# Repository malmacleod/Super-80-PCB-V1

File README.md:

# Super-80 PCB (V1)

This repository stores the KiCad files (schematic and PCB) for the work-in-progress task of creating a reproduction of the Super 80 Computer.

The schematic is fully drawn.

As at 11-OCT-2016, the PCB is about 50% completed.

This will be as close a copy as possible to the original design.  Once this board has been completed, a slightly modified version will then be created, to overcome problems associated with components that are no longer available (such as the keyswitches).

STATUS:

11-OCT-2016: Added bottom layer traces in the vicinity of the 3 24-pin ICs U26, U33 and U42.

10-OCT-2016: Initial upload of KiCad files to Github.

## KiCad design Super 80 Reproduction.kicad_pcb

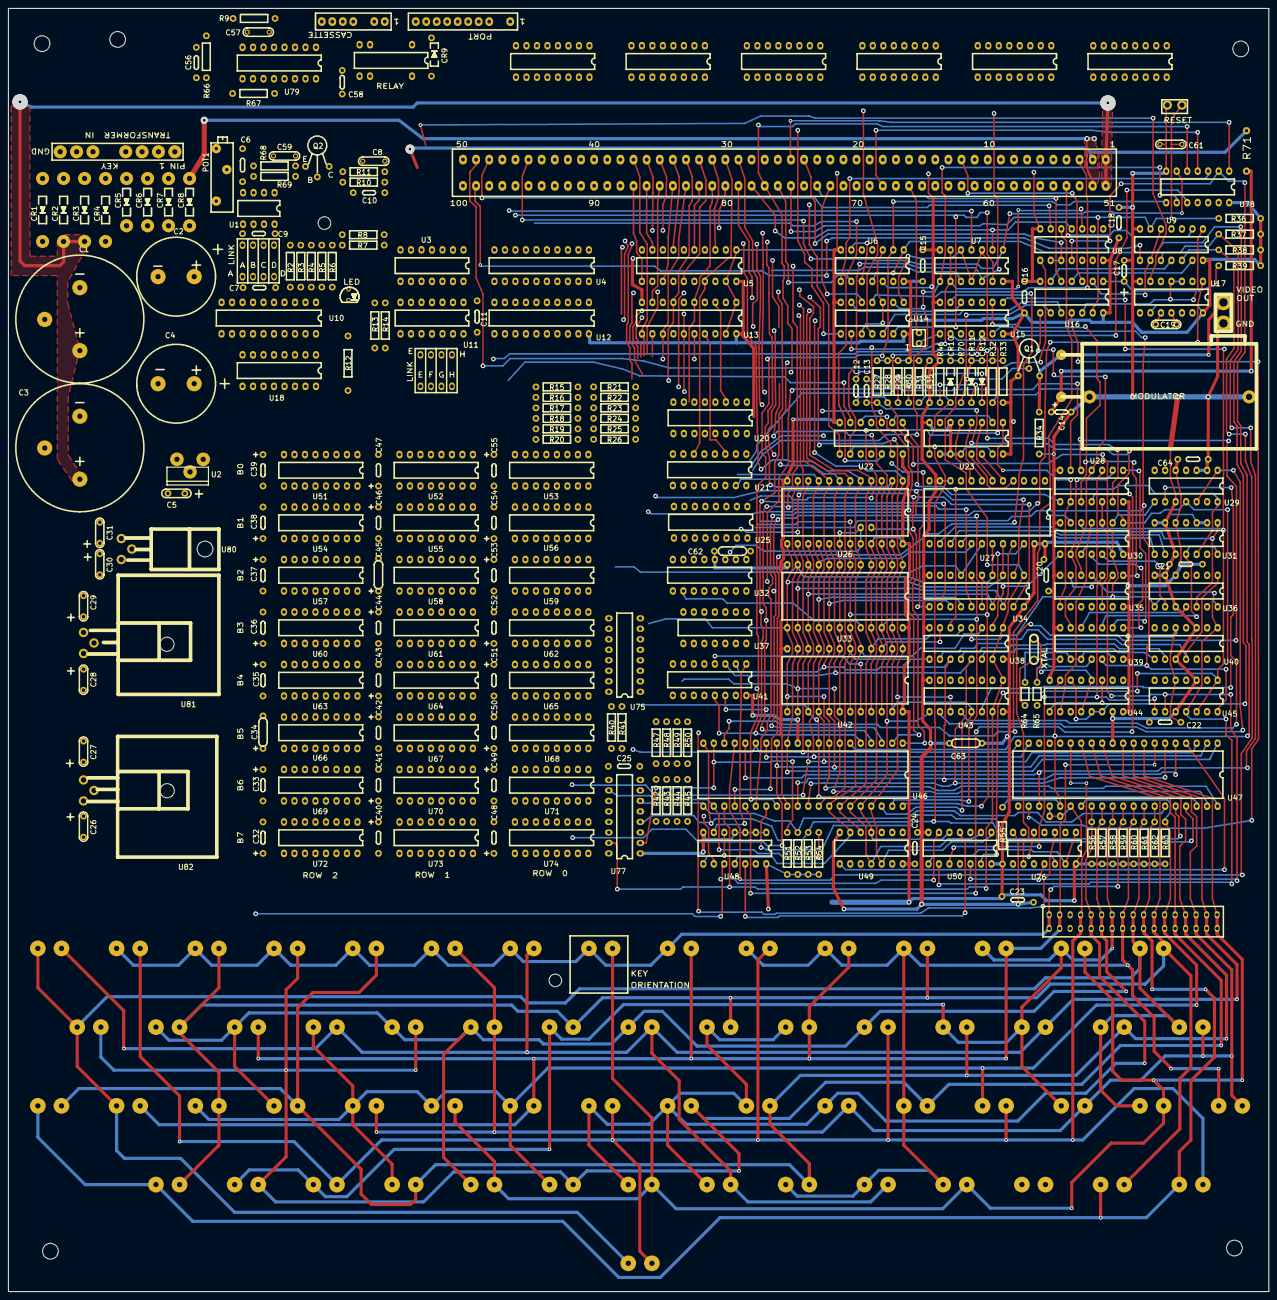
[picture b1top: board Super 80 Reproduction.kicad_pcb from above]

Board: 2 copper layers, 305.0 x 310.5 mm, 312 parts (0 on the bottom side), 281 nets.

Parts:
C1, C3: 5600uF; S80-C1220-POL-600
C2: 1000uF; S80-C2-750-345
C4: 1000uF; S80-C4-750-345
C5: 10uF; S80-C160-POL-32
C6, C21: 0.1uF; S80-C315-32
C7, C9, C63: 0.1uF; S80-C310-32
C8, C57, C59: 0.01uF; S80-C210-32
C10, C11, C15, C16, C22, C25: 0.1uF; S80-C300-32
C12: 68pF; S80-C225-32
C13: 0.01uF; S80-C225-32
C14: 25uF 25V; S80-C190-POL-32
C17: 33uF TANT; S80-C17-200-32
C18, C56, C64: 0.1uF; S80-C290-32
C19: 0.1uF; S80-C200-32-2
C20: 0.1uF; S80-C20-300-32
C23: 0.1uF; S80-C23-300-32
C24: 0.1uF; S80-C24-300-32
C26, C27, C28, C29, C30, C31: 10uF; S80-C200-32-2
C32, C36, C43, C47, C48, C52: 0.1uF; S80-C300-POL-32-A1
C33, C37, C42, C46, C49, C53: 1.5uF TANT; S80-C300-POL-32-B1
C34, C45: 15uF TANT; S80-C310-POL-32-A1
C35, C39, C40, C44, C51, C55: 0.1uF; S80-C300-POL-32-B1
C38, C41, C50, C54: 15uF TANT; S80-C300-POL-32-A1
C58: 0.1uF; S80-C255-32
C61: 0.1uF; S80-C210-32
C62: 0.1uF; S80-C345-32
CR1, CR2, CR3, CR4: MUR420G; S80-D600-50
CR5, CR6, CR7, CR8: 1N4001; S80-D450-50
CR9: 1N914; S80-D365-32
CR10, CR11, CR12: 1N914; S80-D400-32
J1: 8 PIN HEADER; S80-J1-TRANSFORMER
J2: 7 PIN HEADER; S80-J2-CASSETTE
J3: 10 PIN HEADER; S80-J3-PORT
J4: 2 PIN HEADER; S80-J4-VIDEO
J5: S-100 CONNECTOR; S80-S100-CONNECTOR
J6: KEYBOARD CONNECTOR; S80-J6-KEYBRD
JP1: S80-LINK
JP2: JUMPER; S80-JP2
JP3: PRE-LINK; S80-LINK
KEY1, KEY2, KEY3, KEY4, KEY5, KEY6, KEY7, KEY9, KEY10, KEY11, KEY12, KEY13, KEY14, KEY15, KEY16, KEY17, KEY18, KEY19, KEY20, KEY21, KEY22, KEY23, KEY24, KEY25, KEY26, KEY27, KEY28, KEY29, KEY30, KEY32, KEY33, KEY34, KEY35, KEY36, KEY37, KEY38, KEY39, KEY40, KEY41, KEY42, KEY43, KEY44, KEY45, KEY46, KEY48, KEY49, KEY50, KEY51, KEY52, KEY53, KEY54, KEY55, KEY56, KEY57, KEY60, KEY100: S80-KEYSW-A; S80-KEYSW
KEY8: S80-KEYSW-A; S80-KEYSW-OUTLINE
KEY31, KEY47, KEY58, KEY59: S80-KEYSW-B; S80-KEYSW
LED1: 5MM RED LED; S80-LED1
MOD1: UM1082AUS; S80-RF-MOD-ORIG
POT1: 20K; S80-POT1
Q1: BC548; S80-Q1
Q2: BC327; S80-Q2
R2, R3, R4, R5, R6, R36, R39, R56, R57, R58, R59, R60, R61, R62, R63: 4.7K; S80-R400-32
R7: 100K; S80-R400-32
R8: 150R; S80-R400-32
R9: 270K; S80-R400-32
R10, R33, R51, R52, R53, R54: 10K; S80-R400-32
R11: 100R; S80-R400-32
R12: 180R; S80-R520-32
R13: 330; S80-R430-32
R14: 33; S80-R430-32
R15, R16, R17, R18, R19, R20, R41, R42, R43, R44, R45: 33R; S80-R400-32
R21, R22, R23, R24, R25, R26, R31, R40, R47, R48, R49, R50: 330R; S80-R400-32
R27, R28: 2.2K; S80-R400-32
R29, R30: 33K; S80-R400-32
R32, R70: 3.3K; S80-R400-32
R34: 56R; S80-R400-32
R35, R46: 15K; S80-R400-32
R37, R38: 1K; S80-R400-32
R55: 330R; S80-R540-32
R64, R65: 1K; S80-R220-32
R66: 22K; S80-R400-32
R67: 27K; S80-R400-32
R68: 47K; S80-R400-32
R69: 68K; S80-R400-32
R71: 270R 1W ??; S80-R71-385-32
RELAY1: 14-PIN DIL 5V SPDT RELAY; S80-RELAY-DIP-14
Ref**: H*; S80-HOLE-150
Ref**#2, Ref**#3: H*; S80-HOLE-120
Ref**#4, Ref**#5, Ref**#6, Ref**#7: H*; S80-HOLE-150
SW1: 4-WAY DIP SWITCH; S80-SW1-ABCD
SW2: 4-WAY DIP SWITCH; S80-SW2-EFGH
SW3: PCB MOM SW 2-PIN; S80-SW-RESET
U1: LM311; S80-DIP-8-300
U2: 7905T; S80-U2-7905
U3, U7, U78: 74LS02; S80-DIP-14-300
U4, U5, U10, U12, U13: 81LS95; S80-DIP-20-300
U6, U76: 74LS74; S80-DIP-14-300
U8, U15, U22, U39: 74LS04; S80-DIP-14-300
U9: 74LS05; S80-DIP-14-300
U11, U35, U49: 74LS30; S80-DIP-14-300
U14, U28, U37: 74LS00; S80-DIP-14-300
U16: 74LS14; S80-DIP-14-300
U17: 74121; S80-DIP-14-300
U18: 74LS174; S80-DIP-16-300
U20, U21: 74157; S80-DIP-16-300
U23: 74LS165; S80-DIP-16-300
U25, U44, U75: 74109; S80-DIP-16-300
U26: 2516 or 2532; S80-DIP-24-600
U27: 2513; S80-DIP-24-600
U29, U40, U45: 74LS93; S80-DIP-14-300
U30: 74LS86; S80-DIP-14-300
U31: 74LS90; S80-DIP-14-300
U32: 74LS138; S80-DIP-16-300
U33, U42: 2532; S80-DIP-24-600
U34: 74LS374; S80-DIP-20-300
U36: 74LS92; S80-DIP-14-300
U38, U43, U77: 74LS367; S80-DIP-16-300
U41: 74LS139; S80-DIP-16-300
U46: Z80 CPU; S80-DIP-40-600
U47: Z80 PIO; S80-DIP-40-600
U48: 74LS27; S80-DIP-14-300
U50: 74LS20; S80-DIP-14-300
U51, U52, U53, U54, U55, U56, U57, U58, U59, U60, U61, U62, U63, U64, U65, U66, U67, U68, U69, U70, U71, U72, U73, U74: 4116; S80-DIP-16-300
U79: 4046; S80-DIP-16-300
U80: 7812T; S80-U80-7812
U81: 7805T; S80-U81-7805
U82: 7805T; S80-U82-7805
XTAL1: 12MHz; S80-XTAL

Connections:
6LATCH*: U22.5, U41.4
12MHz: U15.13, U25.12, U39.12, U45.14
12MHz*: U15.12, U25.4, U75.4, U75.12, U76.3
+8V: C1.1, C3.1, C27.1, C29.1, CR2.2, CR3.2, J5.1, J5.51, U81.VI, U82.VI
+16V: C2.1, C31.1, CR6.2, CR7.2, J3.3, J5.2, R71.1, U80.VI
-16V: C4.2, CR5.1, CR8.1, J3.1, J5.52, U2.VI
/CPU & ROM/A0: U13.2, U26.8, U33.8, U38.11, U41.2, U42.8, U46.30, U47.5
/CPU & ROM/A1: U13.16, U26.7, U33.7, U38.13, U41.3, U42.7, U46.31, U47.6
/CPU & ROM/A2: U13.4, U26.6, U33.6, U38.9, U42.6, U46.32
/CPU & ROM/A3: U5.2, U26.5, U33.5, U38.3, U42.5, U46.33, U48.11, U49.6
/CPU & ROM/A4: U5.18, U26.4, U33.4, U38.5, U42.4, U46.34, U49.5
/CPU & ROM/A5: U13.18, U26.3, U33.3, U38.7, U42.3, U46.35, U49.11, U50.2
/CPU & ROM/A6: U5.4, U26.2, U33.2, U42.2, U43.9, U46.36, U49.4, U50.5
/CPU & ROM/A7: U13.14, U26.1, U33.1, U42.1, U43.11, U46.37, U49.12, U50.1
/CPU & ROM/A8: U5.14, U26.23, U33.23, U42.23, U43.13, U46.38
/CPU & ROM/A9: U5.6, U26.22, U33.22, U34.6, U42.22, U46.39
/CPU & ROM/A10: U13.12, U26.19, U33.19, U34.5, U42.19, U46.40
/CPU & ROM/A11: JP1.2, U5.12, U34.2, U46.1
/CPU & ROM/A12: U13.6, U32.1, U34.19, U46.2
/CPU & ROM/A13: U13.8, U32.2, U34.16, U46.3
/CPU & ROM/A14: U5.8, U34.15, U37.2, U41.14, U46.4
/CPU & ROM/A15: U5.16, U34.12, U37.1, U41.13, U46.5
/CPU & ROM/D0: U4.11, U10.3, U12.12, U18.3, U26.9, U27.17, U33.9, U42.9, U46.14, U47.19, U51.2, U51.14, U52.2, U52.14, U53.2, U53.14
/CPU & ROM/D1: U4.9, U10.9, U12.8, U18.4, U26.10, U27.18, U33.10, U34.7, U42.10, U46.15, U47.20, U54.2, U54.14, U55.2, U55.14, U56.2, U56.14
/CPU & ROM/D2: U4.17, U10.13, U12.18, U18.6, U26.11, U27.19, U33.11, U34.4, U42.11, U46.12, U47.1, U57.2, U57.14, U58.2, U58.14, U59.2, U59.14
/CPU & ROM/D3: U4.15, U12.16, U18.11, U26.13, U27.20, U33.13, U34.3, U42.13, U46.8, U47.40, U60.2, U60.14, U61.2, U61.14, U62.2, U62.14
/CPU & ROM/D4: U4.3, U10.17, U12.2, U18.13, U26.14, U27.21, U33.14, U34.18, U42.14, U46.7, U47.39, U63.2, U63.14, U64.2, U64.14, U65.2, U65.14
/CPU & ROM/D5: U4.5, U10.5, U12.4, U18.14, U26.15, U27.22, U33.15, U34.17, U42.15, U46.9, U47.38, U66.2, U66.14, U67.2, U67.14, U68.2, U68.14
/CPU & ROM/D6: U4.7, U10.15, U12.6, U26.16, U33.16, U34.14, U42.16, U46.10, U47.3, U69.2, U69.14, U70.2, U70.14, U71.2, U71.14
/CPU & ROM/D7: U4.13, U10.7, U12.14, U26.17, U33.17, U34.13, U42.17, U46.13, U47.2, U72.2, U72.14, U73.2, U73.14, U74.2, U74.14
/CPU & ROM/IOREQ*: R53.1, U46.20, U47.36, U77.4
/CPU & ROM/MEMREQ*: R51.1, U46.19, U77.2
/CPU & ROM/PA0: J6.7, J6.8, KEY2.2, KEY10.2, KEY26.2, KEY38.2, KEY43.2, KEY49.2, KEY59.2, KEY60.2, U47.15
/CPU & ROM/PA1: J6.21, J6.22, KEY3.2, KEY12.2, KEY15.2, KEY17.2, KEY22.2, KEY24.2, KEY33.2, KEY47.2, KEY58.2, U47.14
/CPU & ROM/PA2: J6.25, J6.26, KEY4.2, KEY16.2, KEY20.2, KEY39.2, KEY42.2, KEY48.2, KEY52.2, U47.13
/CPU & ROM/PA3: J6.27, J6.28, KEY5.2, KEY27.2, KEY29.2, KEY31.2, KEY34.2, KEY40.2, KEY50.2, KEY55.2, U47.12
/CPU & ROM/PA4: J6.29, J6.30, KEY6.2, KEY21.2, KEY30.2, KEY35.2, KEY41.2, KEY44.2, KEY46.2, U47.10
/CPU & ROM/PA5: J6.31, J6.32, KEY1.2, KEY7.2, KEY19.2, KEY23.2, KEY28.2, KEY54.2, KEY56.2, U47.9
/CPU & ROM/PA6: J6.33, J6.34, KEY8.2, KEY14.2, KEY36.2, KEY45.2, KEY51.2, KEY53.2, KEY57.2, U47.8
/CPU & ROM/PA7: J6.3, J6.4, KEY9.2, KEY11.2, KEY13.2, KEY18.2, KEY25.2, KEY32.2, KEY37.2, U47.7
/CPU & ROM/PB0: J6.23, J6.24, KEY19.1, KEY33.1, KEY35.1, KEY36.1, KEY37.1, KEY43.1, KEY50.1, KEY52.1, R63.1, U47.27
/CPU & ROM/PB1: J6.9, J6.10, KEY24.1, KEY25.1, KEY38.1, KEY39.1, KEY40.1, KEY41.1, KEY53.1, KEY54.1, R56.1, U47.28
/CPU & ROM/PB2: J6.11, J6.12, KEY17.1, KEY18.1, KEY20.1, KEY21.1, KEY23.1, KEY26.1, KEY34.1, KEY51.1, R57.1, U47.29
/CPU & ROM/PB3: J6.13, J6.14, KEY13.1, KEY14.1, KEY22.1, KEY27.1, KEY28.1, KEY44.1, KEY48.1, KEY49.1, R58.1, U47.30
/CPU & ROM/PB4: J6.1, J6.2, KEY2.1, KEY3.1, KEY4.1, KEY5.1, KEY6.1, KEY7.1, KEY8.1, KEY9.1, R59.1, U47.31
/CPU & ROM/PB5: J6.15, J6.16, KEY10.1, KEY11.1, KEY12.1, KEY42.1, KEY46.1, KEY55.1, KEY56.1, KEY57.1, R60.1, U47.32
/CPU & ROM/PB6: J6.17, J6.18, KEY1.1, KEY15.1, KEY16.1, KEY29.1, KEY30.1, KEY32.1, KEY45.1, KEY60.1, R61.1, U47.33
/CPU & ROM/PB7: J6.19, J6.20, KEY31.1, KEY47.1, KEY58.1, KEY59.1, R62.1, U47.34
/CPU & ROM/RD*: R52.1, U46.21, U47.35, U77.6, U77.11
/CPU & ROM/WR*: R54.1, U46.22, U77.10
/I/O/32K*: R3.1, SW1.6, U10.16
/I/O/48K*: R2.1, SW1.5, U10.6
/I/O/JP BASIC*: R4.1, SW1.7, U10.4
/I/O/PORT-5: J3.5, U18.12
/I/O/PORT-6: J3.6, U18.10
/I/O/PORT-7: J3.7, U10.8
/I/O/PORT-8: J3.8, U10.14
/I/O/TEST*: R5.1, SW1.8, U10.18
/RAM/AA0: R16.2, R22.1, U20.4
/RAM/AA1: R15.2, R21.1, U20.7
/RAM/AA2: R18.2, R24.1, U20.9
/RAM/AA3: R17.2, R23.1, U20.12
/RAM/AA4: R20.2, R26.1, U21.7
/RAM/AA5: R19.2, R25.1, U21.4
/RAM/AA6: R40.1, R41.1, U21.9
/RAM/BAA0: R16.1, U51.5, U52.5, U53.5, U54.5, U55.5, U56.5, U57.5, U58.5, U59.5, U60.5, U61.5, U62.5, U63.5, U64.5, U65.5, U66.5, U67.5, U68.5, U69.5, U70.5, U71.5, U72.5, U73.5, U74.5
/RAM/BAA1: R15.1, U51.12, U52.12, U53.12, U54.12, U55.12, U56.12, U57.12, U58.12, U59.12, U60.12, U61.12, U62.12, U63.12, U64.12, U65.12, U66.12, U67.12, U68.12, U69.12, U70.12, U71.12, U72.12, U73.12, U74.12
/RAM/BAA2: R18.1, U51.6, U52.6, U53.6, U54.6, U55.6, U56.6, U57.6, U58.6, U59.6, U60.6, U61.6, U62.6, U63.6, U64.6, U65.6, U66.6, U67.6, U68.6, U69.6, U70.6, U71.6, U72.6, U73.6, U74.6
/RAM/BAA3: R17.1, U51.11, U52.11, U53.11, U54.11, U55.11, U56.11, U57.11, U58.11, U59.11, U60.11, U61.11, U62.11, U63.11, U64.11, U65.11, U66.11, U67.11, U68.11, U69.11, U70.11, U71.11, U72.11, U73.11, U74.11
/RAM/BAA4: R20.1, U51.7, U52.7, U53.7, U54.7, U55.7, U56.7, U57.7, U58.7, U59.7, U60.7, U61.7, U62.7, U63.7, U64.7, U65.7, U66.7, U67.7, U68.7, U69.7, U70.7, U71.7, U72.7, U73.7, U74.7
/RAM/BAA5: R19.1, U51.10, U52.10, U53.10, U54.10, U55.10, U56.10, U57.10, U58.10, U59.10, U60.10, U61.10, U62.10, U63.10, U64.10, U65.10, U66.10, U67.10, U68.10, U69.10, U70.10, U71.10, U72.10, U73.10, U74.10
/RAM/BAA6: R41.2, U51.13, U52.13, U53.13, U54.13, U55.13, U56.13, U57.13, U58.13, U59.13, U60.13, U61.13, U62.13, U63.13, U64.13, U65.13, U66.13, U67.13, U68.13, U69.13, U70.13, U71.13, U72.13, U73.13, U74.13
/RAM/CAS0*: R45.2, U53.15, U56.15, U59.15, U62.15, U65.15, U68.15, U71.15, U74.15
/RAM/CAS1*: R44.2, U52.15, U55.15, U58.15, U61.15, U64.15, U67.15, U70.15, U73.15
/RAM/CAS2*: R43.2, U51.15, U54.15, U57.15, U60.15, U63.15, U66.15, U69.15, U72.15
/RAM/RAS*: R42.2, U51.4, U52.4, U53.4, U54.4, U55.4, U56.4, U57.4, U58.4, U59.4, U60.4, U61.4, U62.4, U63.4, U64.4, U65.4, U66.4, U67.4, U68.4, U69.4, U70.4, U71.4, U72.4, U73.4, U74.4
/RAM/S100-A0: J5.79, U13.3, U20.3
/RAM/S100-A1: J5.80, U13.15, U20.6
/RAM/S100-A2: J5.81, U13.5, U20.10
/RAM/S100-A3: J5.31, U5.3, U20.13
/RAM/S100-A4: J5.30, U5.17, U21.6
/RAM/S100-A5: J5.29, U13.17, U21.3
/RAM/S100-A6: J5.82, U5.5, U21.10
/RAM/S100-A7: J5.83, U13.13, U20.2
/RAM/S100-A8: J5.84, U5.13, U20.5
/RAM/S100-A9: J5.34, U5.7, U20.11
/RAM/S100-A10: J5.37, U13.11, U20.14
/RAM/S100-A11: J5.87, U5.11, U21.5
/RAM/S100-A12: J5.33, U13.7, U21.2
/RAM/S100-A13: J5.85, U13.9, U21.11
/S-100 Interface/S100-A14: J5.86, U5.9
/S-100 Interface/S100-A15: J5.32, U5.15
/S-100 Interface/S100-CLK-B*: J5.24, U8.9, U8.10
/S-100 Interface/S100-CLOCK-B*: J5.49, U8.8
/S-100 Interface/S100-DI0: J5.95, U4.12
/S-100 Interface/S100-DI1: J5.94, U4.8
/S-100 Interface/S100-DI2: J5.41, U4.18
/S-100 Interface/S100-DI3: J5.42, U4.16
/S-100 Interface/S100-DI4: J5.91, U4.2
/S-100 Interface/S100-DI5: J5.92, U4.4
/S-100 Interface/S100-DI6: J5.93, U4.6
/S-100 Interface/S100-DI7: J5.43, U4.14
/S-100 Interface/S100-DIN*: U4.19, U11.8
/S-100 Interface/S100-DO0: J5.36, U12.11
/S-100 Interface/S100-DO1: J5.35, U12.9
/S-100 Interface/S100-DO2: J5.88, U12.17
/S-100 Interface/S100-DO3: J5.89, U12.15
/S-100 Interface/S100-DO4: J5.38, U12.3
/S-100 Interface/S100-DO5: J5.39, U12.5
/S-100 Interface/S100-DO6: J5.40, U12.7
/S-100 Interface/S100-DO7: J5.90, U12.13
/S-100 Interface/S100-INT*: J5.73, U16.5
/S-100 Interface/S100-NMI*: J5.12, U16.3
/S-100 Interface/S100-POC*: J5.99, U9.8
/S-100 Interface/S100-PRFSH*: J5.66, JP2.1
/S-100 Interface/S100-PSTVAL: J5.25, U78.1
/S-100 Interface/S100-PSYNC: J5.76, U6.9
/S-100 Interface/S100-RDY*: J5.72, U14.5
/S-100 Interface/S100-RESET*: C61.2, J5.75, R36.1, SW3.2, U9.6, U16.13
/S-100 Interface/S100-SINTA: J5.96, U7.13, U14.13
/S-100 Interface/S100-SLAVE-CLR*: J5.54, U9.2
/S-100 Interface/S100-SOUT: J5.45, U7.1, U78.6
/S-100 Interface/S100-XRDY*: J5.3, U14.4
AS/W*: SW2.1, U11.4, U25.6
BUSAK*: U16.9, U34.1, U38.1, U38.15, U43.1, U43.15, U46.23, U77.15
BUSREQ*: U28.11, U46.25
C000-FFFF*: U3.5, U25.5, U37.3, U37.4
CLK: R55.1, U8.11, U44.7, U46.6, U47.25, U78.2
CLK2: U6.1, U6.11, U44.6, U44.13, U44.14
DECODEF*: U48.10, U50.6
GND: C1.2, C2.2, C3.2, C4.1, C5.1, C6.2, C7.1, C8.1, C9.1, C11.1, C14.2, C15.1, C16.1, C17.2, C18.1, C20.2, C21.1, C22.1, C23.2, C24.1, C25.2, C26.2, C27.2, C28.2, C29.2, C30.2, C31.2, C32.1, C33.2, C34.1, C35.2, C36.1, C37.2, C38.1, C39.2, C40.2, C41.1, C42.2, C43.1, C44.2, C45.1, C46.2, C47.1, C48.1, C49.2, C50.1, C51.2, C52.1, C53.2, C54.1, C55.2, C58.2, C59.2, C61.1, C62.1, C63.1, C64.2, CR1.1, CR4.1, CR9.1, J1.2, J1.3, J1.8, J2.3, J2.5, J3.4, J4.2, J5.26, J5.50, J5.100, MOD1.3, MOD1.4, POT1.B, R9.1, R11.1, R32.2, R34.2, R35.2, R46.1, R67.1, RELAY1.9, SW1.1, SW1.2, SW1.3, SW1.4, SW3.1, U1.1, U1.4, U2.GND, U3.7, U4.10, U5.1, U5.10, U5.19, U6.7, U6.12, U7.7, U8.7, U9.7, U10.10, U11.7, U12.1, U12.10, U12.19, U13.1, U13.10, U13.19, U14.7, U15.7, U16.7, U17.7, U18.8, U20.8, U20.15, U21.8, U21.15, U22.7, U23.6, U23.8, U23.10, U23.11, U23.12, U23.15, U25.8, U26.12, U27.10, U27.11, U28.7, U29.2, U29.3, U29.10, U30.7, U31.2, U31.3, U31.6, U31.7, U31.10, U32.4, U32.8, U33.12, U34.10, U35.7, U36.6, U36.7, U36.10, U37.7, U38.8, U39.7, U40.2, U40.3, U40.10, U41.8, U42.12, U43.8, U44.8, U44.15, U45.2, U45.3, U45.10, U46.29, U47.11, U48.1, U48.2, U48.3, U48.4, U48.7, U49.7, U50.7, U51.16, U52.16, U53.16, U54.16, U55.16, U56.16, U57.16, U58.16, U59.16, U60.16, U61.16, U62.16, U63.16, U64.16, U65.16, U66.16, U67.16, U68.16, U69.16, U70.16, U71.16, U72.16, U73.16, U74.16, U75.8, U76.7, U77.1, U77.8, U77.12, U78.7, U79.5, U79.8, U80.GND, U81.GND, U82.GND
HALT*: U8.5, U46.18
IEO: U16.11, U47.22
INPORT*: U10.1, U10.19, U41.6
INT*: R37.1, U9.10, U46.16, U47.23
IOREQ-BUFRD*: U7.3, U7.5, U7.11, U14.1, U48.9, U48.13, U77.5
M1*: U3.6, U7.12, U22.9, U46.27, U47.37
MEM: U25.13, U25.14, U32.3, U37.11
MEMREQ-BUFRD*: U7.8, U14.2, U37.12, U77.3, U78.9
MREQ2*: U28.6, U37.13
MRESET: U3.9, U17.6
MRESET*: U17.1, U46.26
unnamed: R43.1, R48.2, U41.10
unnamed: U41.15, U75.7
unnamed: U75.2, U75.3, U75.10
unnamed: R45.1, R50.2, U41.12
unnamed: R44.1, R49.2, U41.11
unnamed: U25.7, U75.13, U75.14
unnamed: U20.1, U21.1, U75.9
unnamed: R42.1, R47.2, U25.2, U25.3, U25.9
unnamed: R8.1, U18.5
unnamed: C10.1, J2.4
unnamed: CR9.2, Q2.C, RELAY1.6
unnamed: R12.2, U18.15
unnamed: Q2.B, R8.2
unnamed: J2.1, RELAY1.13
unnamed: J2.2, RELAY1.7
unnamed: C10.2, R10.2, R11.2
unnamed: R7.1, U18.2
unnamed: C8.2, R7.2, R10.1
unnamed: LED1.2, R12.1
unnamed: C57.2, U79.6
unnamed: C57.1, U79.7
unnamed: R67.2, U79.11
unnamed: R9.2, U79.12
unnamed: U79.3, U79.4
unnamed: R69.2, U79.2
unnamed: C59.1, R68.2, U1.2
unnamed: J2.6, R66.1
unnamed: C56.2, R66.2
unnamed: R68.1, R69.1, U79.9
unnamed: C56.1, U79.14
unnamed: C6.1, POT1.W, U1.3
unnamed: R6.1, U1.7, U10.2
unnamed: U48.5, U48.8
unnamed: U41.1, U48.6
unnamed: U18.9, U22.6
unnamed: U11.11, U14.11
unnamed: SW2.5, U11.1
unnamed: SW2.6, U11.2
unnamed: SW2.7, U11.3
unnamed: SW2.8, U11.12
unnamed: U14.12, U16.10
unnamed: C19.2, U17.11
unnamed: C19.1, U17.10
unnamed: U9.1, U16.12, U17.3, U17.4
unnamed: C17.1, R39.1, U16.1
unnamed: J5.68, U78.4
unnamed: J5.44, U22.8
unnamed: U9.5, U9.9, U16.2
unnamed: U9.11, U16.6
unnamed: U9.13, U16.4
unnamed: JP2.2, U15.8
unnamed: U6.6, U6.10
unnamed: U15.9, U78.10
unnamed: U14.6, U15.5
unnamed: J5.47, U7.10
unnamed: J5.46, U7.4
unnamed: J5.97, U14.8
unnamed: U6.3, U14.3, U14.10
unnamed: J5.48, U8.6
unnamed: U6.8, U78.3
unnamed: J5.78, U7.2, U8.4
unnamed: U23.13, U27.4
unnamed: U23.14, U27.5
unnamed: U23.3, U27.6
unnamed: U23.4, U27.7
unnamed: U23.5, U27.8
unnamed: CR10.1, R31.2, U23.9
unnamed: CR10.2, R70.1
unnamed: U23.1, U28.9, U35.8
unnamed: U15.2, U28.10, U35.1
unnamed: U29.9, U43.12
unnamed: U22.4, U34.11
unnamed: U22.1, U28.8
unnamed: U22.2, U23.2
unnamed: U44.2, U44.3, U44.9
unnamed: U30.4, U44.10
unnamed: U30.6, U44.4, U44.12
unnamed: C14.1, MOD1.2, R71.2
unnamed: J4.1, MOD1.1, Q1.E, R34.1
unnamed: CR11.1, CR12.1, Q1.B, R32.1, R33.1, R70.2
unnamed: C13.1, CR11.2, R30.2, R46.2
unnamed: U29.8, U30.2
unnamed: C12.1, CR12.2, R29.2, R35.1
unnamed: U15.1, U30.5, U45.1, U45.12, U50.13
unnamed: U35.4, U40.1, U45.11, U50.9
unnamed: U30.11, U39.1
unnamed: C13.2, R27.2, U29.11, U30.1, U43.14
unnamed: U29.1, U29.12, U43.10
unnamed: U30.12, U36.9
unnamed: U29.14, U31.12, U38.6
unnamed: U28.2, U30.9, U39.6
unnamed: U28.3, U35.6
unnamed: U28.1, U39.2
unnamed: U27.14, U31.1, U36.12
unnamed: U31.11, U31.14, U39.3
unnamed: R64.2, U39.8, XTAL1.2
unnamed: R64.1, R65.2, U39.9, U39.10, U39.13
unnamed: R65.1, U39.11, XTAL1.1
unnamed: U27.16, U31.8
unnamed: U36.1, U38.10, U40.11
unnamed: U27.15, U31.9
unnamed: U38.12, U40.9
unnamed: U36.11, U39.5
unnamed: U28.5, U76.9
unnamed: U16.8, U28.4, U35.5
unnamed: C12.2, R28.2, U30.10, U30.13, U36.8, U36.14, U38.4
unnamed: U76.5, U76.12
unnamed: U38.14, U40.8
unnamed: U30.8, U38.2
unnamed: U35.11, U39.4
unnamed: U35.2, U45.9, U50.12, U76.11
unnamed: U35.3, U45.8, U50.10
unnamed: U28.12, U30.3, U35.12
unnamed: U50.8, U76.1, U76.13
unnamed: CR3.1, CR4.2, J1.6
unnamed: CR1.2, CR2.1, J1.7
unnamed: CR7.1, CR8.2, J1.1
unnamed: CR5.2, CR6.1, J1.4
unnamed: U32.6, U37.6
unnamed: U3.8, U3.13
unnamed: U3.4, U3.12
unnamed: U48.12, U50.4
unnamed: R13.1, R14.1, U22.12
unnamed: U47.4, U49.8
NMI*: R38.1, U9.12, U46.17
RAM-WR*: R14.2, U51.3, U52.3, U53.3, U54.3, U55.3, U56.3, U57.3, U58.3, U59.3, U60.3, U61.3, U62.3, U63.3, U64.3, U65.3, U66.3, U67.3, U68.3, U69.3, U70.3, U71.3, U72.3, U73.3, U74.3
RD-BUFRD*: U4.1, U7.6, U7.9, U8.3, U14.9, U22.13, U32.5, U77.7
RFSH*: U6.2, U46.28, U75.1, U78.8
ROM0*: JP1.1, SW2.4, U26.18, U26.20, U32.11, U33.18, U42.18
ROM1*: SW2.3, U32.10, U33.20
ROM2*: SW2.2, U32.9, U42.20
SOD*: U3.10, U3.11, U37.5, U75.15
VBB: C5.2, C32.2, C34.2, C36.2, C38.2, C41.2, C43.2, C45.2, C47.2, C48.2, C50.2, C52.2, C54.2, U2.VO, U51.1, U52.1, U53.1, U54.1, U55.1, U56.1, U57.1, U58.1, U59.1, U60.1, U61.1, U62.1, U63.1, U64.1, U65.1, U66.1, U67.1, U68.1, U69.1, U70.1, U71.1, U72.1, U73.1, U74.1
VCC: C7.2, C9.2, C11.2, C15.2, C16.2, C18.2, C20.1, C21.2, C22.2, C23.1, C24.2, C25.1, C26.1, C28.1, C58.1, C62.2, C63.2, C64.1, JP3.1, JP3.2, LED1.1, POT1.F, Q1.C, Q2.E, R2.2, R3.2, R4.2, R5.2, R6.2, R13.2, R21.2, R22.2, R23.2, R24.2, R25.2, R26.2, R27.1, R28.1, R29.1, R30.1, R31.1, R33.2, R36.2, R37.2, R38.2, R39.2, R40.2, R47.1, R48.1, R49.1, R50.1, R51.2, R52.2, R53.2, R54.2, R55.2, R56.2, R57.2, R58.2, R59.2, R60.2, R61.2, R62.2, R63.2, U1.8, U3.14, U4.20, U5.20, U6.14, U7.14, U8.14, U9.14, U10.20, U11.14, U12.20, U13.20, U14.14, U15.14, U16.14, U17.9, U17.14, U18.16, U20.16, U21.16, U22.14, U23.16, U25.16, U26.21, U26.24, U27.23, U27.24, U28.14, U29.5, U30.14, U31.5, U32.16, U33.21, U33.24, U34.20, U35.14, U36.5, U37.14, U38.16, U39.14, U40.5, U41.16, U42.21, U42.24, U43.16, U44.16, U45.5, U46.11, U47.24, U47.26, U48.14, U49.14, U50.14, U51.9, U52.9, U53.9, U54.9, U55.9, U56.9, U57.9, U58.9, U59.9, U60.9, U61.9, U62.9, U63.9, U64.9, U65.9, U66.9, U67.9, U68.9, U69.9, U70.9, U71.9, U72.9, U73.9, U74.9, U75.16, U76.14, U77.16, U78.14, U79.16, U81.VO, U82.VO
VDD: C30.1, C33.1, C35.1, C37.1, C39.1, C40.1, C42.1, C44.1, C46.1, C49.1, C51.1, C53.1, C55.1, U51.8, U52.8, U53.8, U54.8, U55.8, U56.8, U57.8, U58.8, U59.8, U60.8, U61.8, U62.8, U63.8, U64.8, U65.8, U66.8, U67.8, U68.8, U69.8, U70.8, U71.8, U72.8, U73.8, U74.8, U80.VO
VDU-ENABLE: U18.7, U28.13
VDUCONF*: U22.3, U41.5
WAIT*: U15.6, U46.24
WR-BUFRD*: J5.77, U77.9, U78.5

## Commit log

2016-10-10 Add files via upload
    Snapshot of work-in-progress version as at Mon 10.10.2016
2016-10-11 Add files via upload
    Added bottom layer traces in the vicinity of the 3 24-pin ICs U26, U33 and U42.
2016-10-11 Add files via upload
    Reflects additional PCB traces added on 11.10.2016 (mostly bottom layer in the vicinity of the ICs U6 to U22).
2016-10-11 Add files via upload
    Updated library files
2016-10-14 Add files via upload
    Added top layer tracks in the vicinity of U5 and U13.
